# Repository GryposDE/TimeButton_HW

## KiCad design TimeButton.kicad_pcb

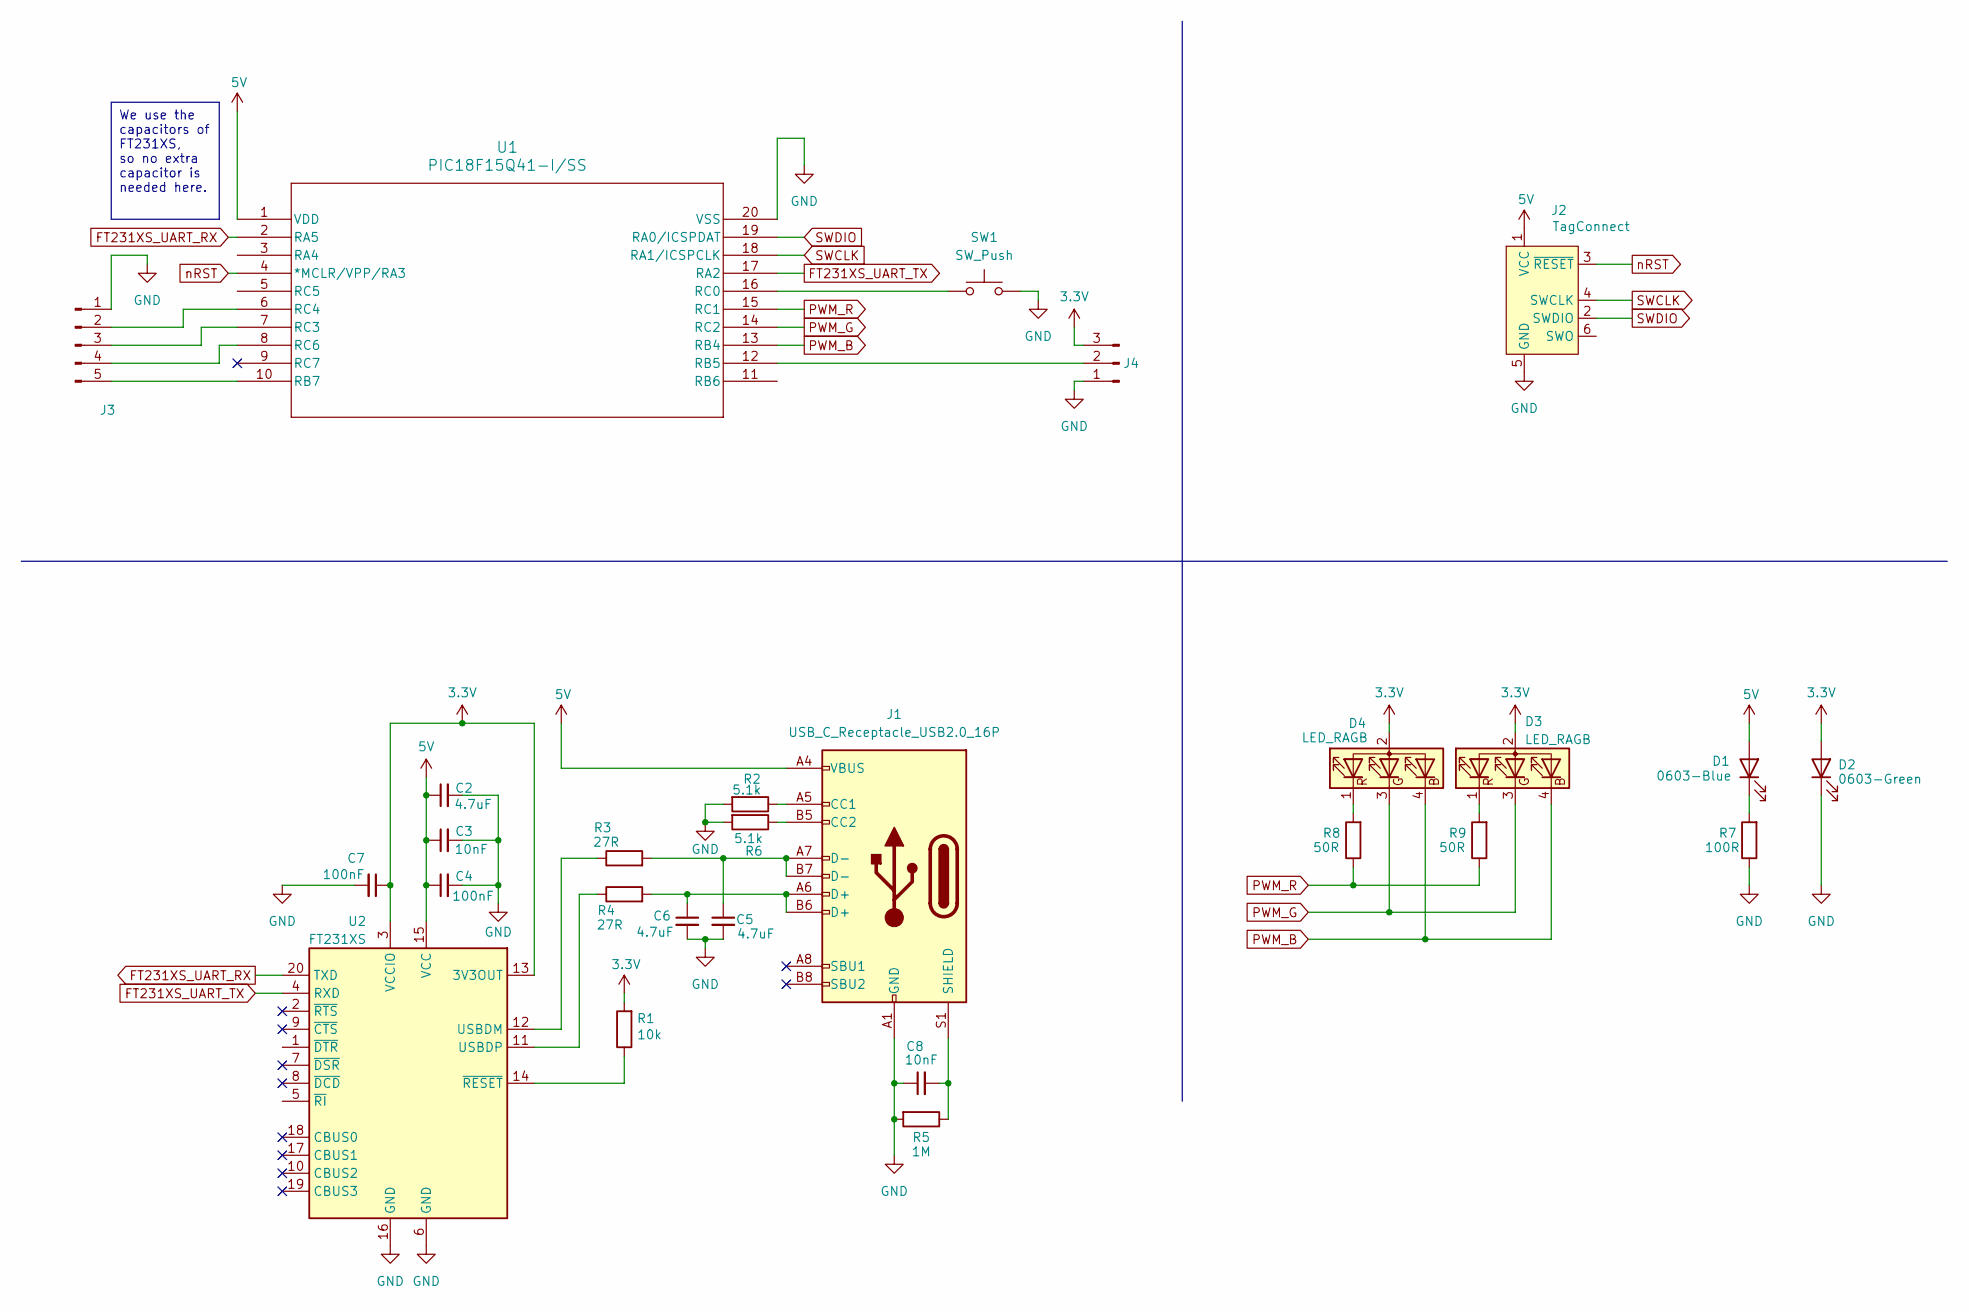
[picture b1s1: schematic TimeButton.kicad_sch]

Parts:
C2, C5, C6: 4.7uF; C_0805_2012Metric_Pad1.18x1.45mm_HandSolder
C3, C8: 10nF; C_0805_2012Metric_Pad1.18x1.45mm_HandSolder
C4, C7: 100nF; C_0805_2012Metric_Pad1.18x1.45mm_HandSolder
D1: 0603-Blue; LED_0805_2012Metric_Pad1.15x1.40mm_HandSolder
D2: 0603-Green; LED_0805_2012Metric_Pad1.15x1.40mm_HandSolder
D3, D4: LED_RAGB; LED_D5.0mm-4_RGB_Wide_Pins
J1: USB_C_Receptacle_USB2.0_16P; USB_C_Receptacle_G-Switch_GT-USB-7010ASV
J2: TagConnect; Tag-Connect_TC2030-IDC-NL_2x03_P1.27mm_Vertical
J3: Conn_01x05_Pin; PinHeader_1x05_P2.00mm_Vertical
J4: Conn_01x03_Pin; PinHeader_1x03_P2.00mm_Vertical
R1: 10k; R_0805_2012Metric_Pad1.20x1.40mm_HandSolder
R2, R6: 5.1k; R_0805_2012Metric_Pad1.20x1.40mm_HandSolder
R3, R4: 27R; R_0805_2012Metric_Pad1.20x1.40mm_HandSolder
R5: 1M; R_0805_2012Metric_Pad1.20x1.40mm_HandSolder
R7: 100R; R_0805_2012Metric_Pad1.20x1.40mm_HandSolder
R8, R9: 50R; R_0805_2012Metric_Pad1.20x1.40mm_HandSolder
SW1: SW_Push; SW_PUSH-12mm
U1: PIC18F15Q41-I/SS; SSOP20_SS_MCH
U2: FT231XS; SSOP-20_3.9x8.7mm_P0.635mm

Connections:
3.3V: C7.1, D2.2 (A), D3.2 (A), D4.2 (A), J4.3, R1.2, U2.3 (VCCIO), U2.13 (3V3OUT); also elsewhere on the board
5V: C2.1, C3.1, C4.1, D1.2 (A), J1.A4 (VBUS), J1.A9 (VBUS), J1.B4 (VBUS), J1.B9 (VBUS), J2.1 (VCC), U1.1 (VDD), U2.15 (VCC); also elsewhere on the board
FT231XS_UART_RX: U1.2 (RA5), U2.20 (TXD)
FT231XS_UART_TX: U1.17 (RA2), U2.4 (RXD)
GND: C2.2, C3.2, C4.2, C5.2, C6.2, C7.2, C8.1, D2.1 (K), J1.A1 (GND), J1.A12 (GND), J1.B1 (GND), J1.B12 (GND), J2.5 (GND), J3.1, J4.1, R2.2, R5.2, R6.2, R7.1, SW1.1, U1.20 (VSS), U2.6 (GND), U2.16 (GND); also elsewhere on the board
unnamed: C5.1, J1.A7 (D-), J1.B7 (D-), R3.2
unnamed: C6.1, J1.A6 (D+), J1.B6 (D+), R4.2
unnamed 7: D1.1 (K), R7.2; also elsewhere on the board
unnamed: D3.1 (RK), R9.2
unnamed: D4.1 (RK), R8.2
unnamed: J1.A5 (CC1), R2.1
unnamed: J1.B5 (CC2), R6.1
unnamed: C8.2, J1.S1 (SHIELD), R5.1
unnamed: J3.2, U1.6 (RC4)
unnamed: J3.3, U1.7 (RC3)
unnamed: J3.4, U1.8 (RC6)
unnamed: J3.5, U1.10 (RB7)
unnamed: J4.2, U1.12 (RB5)
unnamed: SW1.2, U1.16 (RC0)
unnamed: R3.1, U2.12 (USBDM)
unnamed: R4.1, U2.11 (USBDP)
unnamed: R1.1, U2.14 (~RESET)
PWM_B: D3.4 (BK), D4.4 (BK), U1.13 (RB4)
PWM_G: D3.3 (GK), D4.3 (GK), U1.14 (RC2)
PWM_R: R8.1, R9.1, U1.15 (RC1)
SWCLK: J2.4 (SWCLK), U1.18 (RA1/ICSPCLK)
SWDIO: J2.2 (SWDIO), U1.19 (RA0/ICSPDAT)
nRST: J2.3 (~RESET), U1.4 (*MCLR/VPP/RA3)

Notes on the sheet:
We use the capacitors of FT231XS, so no extra capacitor is needed here.

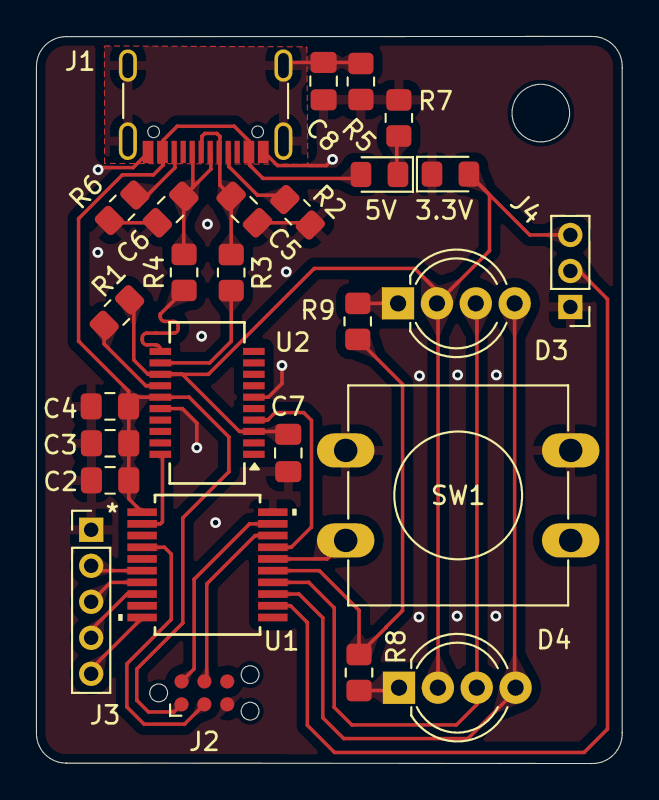
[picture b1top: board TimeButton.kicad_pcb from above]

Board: 2 copper layers, 32.5 x 40.4 mm, 27 parts (0 on the bottom side), 28 nets.

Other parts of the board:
3.3V: 0603-Green; LED_0805_2012Metric_Pad1.15x1.40mm_HandSolder
5V: 0603-Blue; LED_0805_2012Metric_Pad1.15x1.40mm_HandSolder

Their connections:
3.3V: 3.3V.2 (A); also elsewhere on the board
5V: 5V.2 (A); also elsewhere on the board
GND: 3.3V.1 (K); also elsewhere on the board
unnamed 7: 5V.1 (K); also elsewhere on the board

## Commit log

2025-04-29 Added UART_2_USB schematics
2025-04-29 Changed USB_C connector from 6Pin to 16Pin
2025-04-29 Added gitignore
2025-04-29 Added LEDs
2025-04-29 Added TagConnect connections in the schematic
2025-04-29 Layout v1.0
2025-05-01 Added UART connection to FT231XS + changed some pin outputs as a result to fit it into the design
2025-05-01 Updated layout
